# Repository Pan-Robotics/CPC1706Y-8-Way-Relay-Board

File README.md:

# CPC1706Y-8-Way-Relay-Board
CPC1706Y 8 Way Solid State Relay Board

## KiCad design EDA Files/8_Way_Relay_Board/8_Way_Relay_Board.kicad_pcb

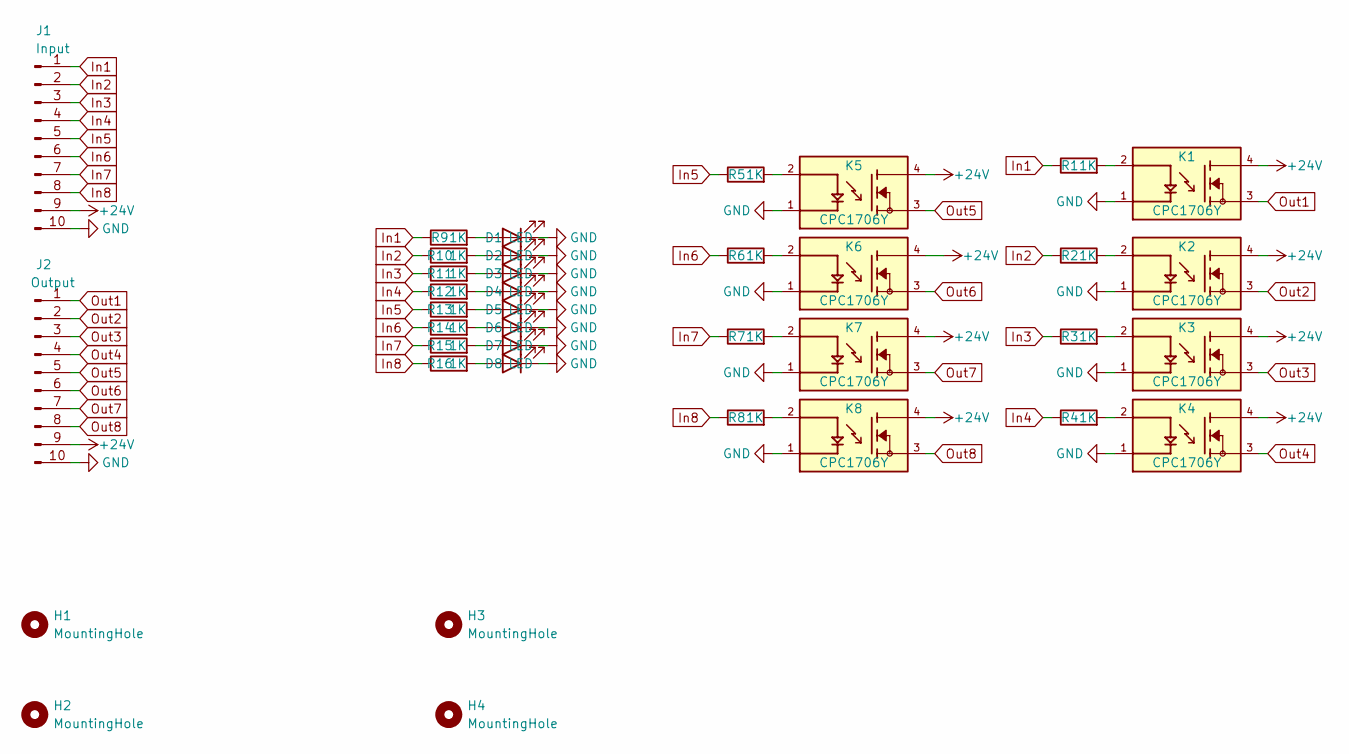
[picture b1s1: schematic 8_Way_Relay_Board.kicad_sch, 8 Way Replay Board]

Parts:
D1, D2, D3, D4, D5, D6, D7, D8: LED; LED_1206_3216Metric_Pad1.42x1.75mm_HandSolder
H1, H2, H3, H4: MountingHole; MountingHole_3.2mm_M3
J1: Input; PhoenixContact_MCV_1,5_10-G-3.5_1x10_P3.50mm_Vertical
J2: Output; PhoenixContact_MCV_1,5_10-G-3.5_1x10_P3.50mm_Vertical
K1, K2, K3, K4, K5, K6, K7, K8: CPC1706Y; CPC1706Y_IXY
R1, R2, R3, R4, R5, R6, R7, R8, R9, R10, R11, R12, R13, R14, R15, R16: 1K; R_0805_2012Metric_Pad1.20x1.40mm_HandSolder

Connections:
+24V: J1.9, J2.9, K1.4, K2.4, K3.4, K4.4, K5.4, K6.4, K7.4, K8.4
GND: D1.1 (K), D2.1 (K), D3.1 (K), D4.1 (K), D5.1 (K), D6.1 (K), D7.1 (K), D8.1 (K), J1.10, J2.10, K1.1, K2.1, K3.1, K4.1, K5.1, K6.1, K7.1, K8.1
In1: J1.1, R1.1, R9.1
In2: J1.2, R2.1, R10.1
In3: J1.3, R3.1, R11.1
In4: J1.4, R4.1, R12.1
In5: J1.5, R5.1, R13.1
In6: J1.6, R6.1, R14.1
In7: J1.7, R7.1, R15.1
In8: J1.8, R8.1, R16.1
unnamed: D1.2 (A), R9.2
unnamed: D2.2 (A), R10.2
unnamed: D3.2 (A), R11.2
unnamed: D4.2 (A), R12.2
unnamed: D5.2 (A), R13.2
unnamed: D6.2 (A), R14.2
unnamed: D7.2 (A), R15.2
unnamed: D8.2 (A), R16.2
unnamed: K1.2, R1.2
unnamed: K2.2, R2.2
unnamed: K3.2, R3.2
unnamed: K4.2, R4.2
unnamed: K5.2, R5.2
unnamed: K6.2, R6.2
unnamed: K7.2, R7.2
unnamed: K8.2, R8.2
Out1: J2.1, K1.3
Out2: J2.2, K2.3
Out3: J2.3, K3.3
Out4: J2.4, K4.3
Out5: J2.5, K5.3
Out6: J2.6, K6.3
Out7: J2.7, K7.3
Out8: J2.8, K8.3

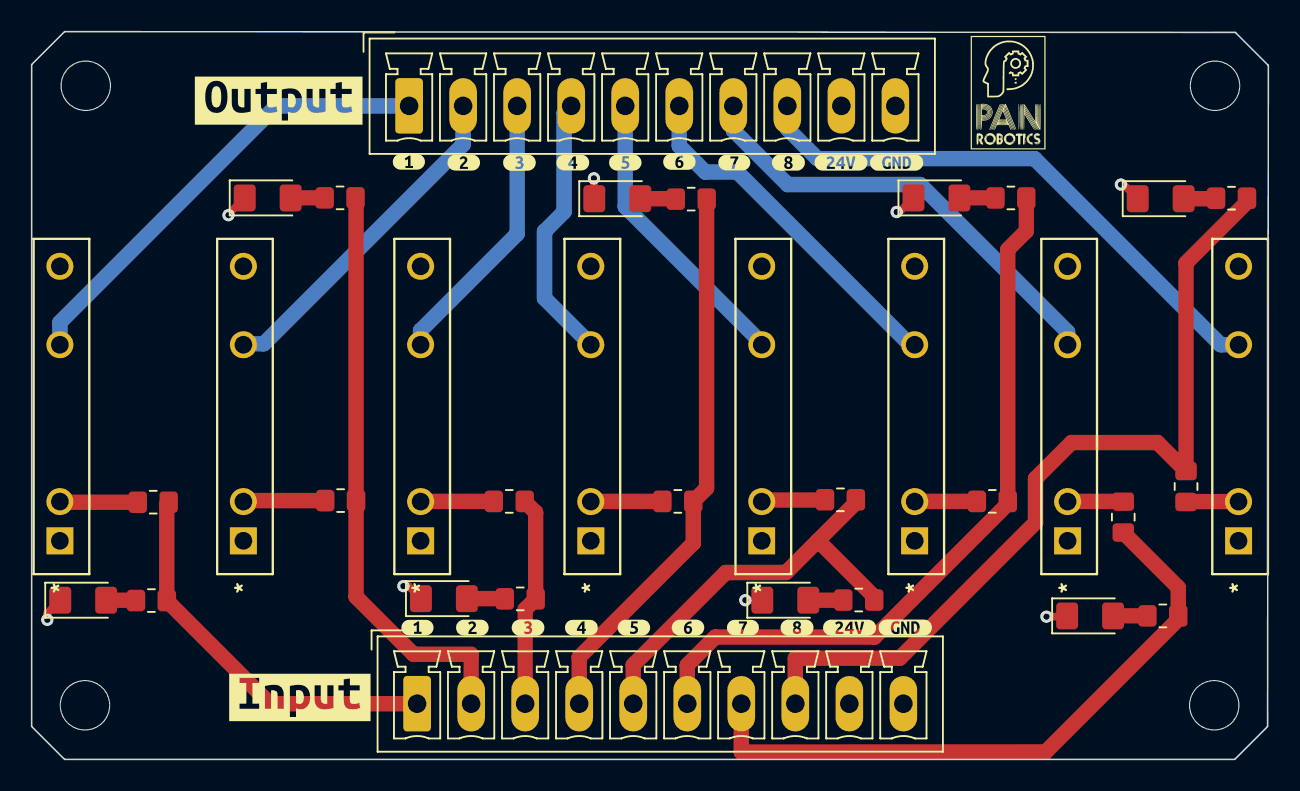
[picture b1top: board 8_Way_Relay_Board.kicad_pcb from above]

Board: 4 copper layers, 80.1 x 47.1 mm, 60 parts (0 on the bottom side), 34 nets.

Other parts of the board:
kibuzzard-66A00A0B, kibuzzard-66A00A0B#2: G***; kibuzzard-66A00A0B
kibuzzard-66A00A1A, kibuzzard-66A00A1A#2: G***; kibuzzard-66A00A1A
kibuzzard-66A00A6B, kibuzzard-66A00A6B#2: G***; kibuzzard-66A00A6B
kibuzzard-66A00A14, kibuzzard-66A00A14#2: G***; kibuzzard-66A00A14
kibuzzard-66A00A22, kibuzzard-66A00A22#2: G***; kibuzzard-66A00A22
kibuzzard-66A00A29, kibuzzard-66A00A29#2: G***; kibuzzard-66A00A29
kibuzzard-66A00A30, kibuzzard-66A00A30#2: G***; kibuzzard-66A00A30
kibuzzard-66A00A45, kibuzzard-66A00A45#2: G***; kibuzzard-66A00A45
kibuzzard-66A00A61, kibuzzard-66A00A61#2: G***; kibuzzard-66A00A61
kibuzzard-66A00AFA: G***; kibuzzard-66A00AFA
kibuzzard-66A00B14: G***; kibuzzard-66A00B14
kibuzzard-66A009AB, kibuzzard-66A009AB#2: G***; kibuzzard-66A009AB

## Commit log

2024-07-23 initial upload
